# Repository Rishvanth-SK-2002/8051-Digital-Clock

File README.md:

# 8051 Digital Clock with Alarm

A bare-metal digital clock and alarm project built around the Nuvoton **W78E052DDG**, an 8051-compatible microcontroller. The project combines firmware, a custom two-layer through-hole PCB, display multiplexing, push-button UI, an audible alarm, and multiple PCB revisions.

## Project highlights

- Nuvoton W78E052DDG 8051-compatible MCU
- 11.0592 MHz clock source
- Six multiplexed 7-segment displays
- Six discrete BC547 digit drivers
- 6-position user interface: LEFT / RIGHT / UP / DOWN / MODE / TIMESET/ALARM selection
- Timer0-driven software time base
- External interrupt 0 used for entering configuration mode
- Alarm time comparison and buzzer output
- 2-layer through-hole PCB developed through multiple revisions
- Final PCB source, schematic, and manufacturing Gerbers included
- Firmware is written in 8051 assembly

## Repository structure

```text
.
├── firmware/
│   ├── digclock.asm
│   ├── MEMORY_MAP.md
│   ├── FIRMWARE_ARCHITECTURE.md
│   ├── README.md
├── hardware/
│   ├── schematic/
│   │   ├── digclock.kicad_sch
│   │   ├── digclock.kicad_pro
│   │   ├── digclock-eagle-import.kicad_sym
│   │   └── sym-lib-table
│   ├── pcb/
│   │   ├── final/
│   │   │   └── digclock.kicad_pcb
│   │   └── revisions/
│   │       ├── v1/digclockv1.kicad_pcb
│   │       ├── v2/digclockv2.kicad_pcb
│   │       ├── v3/digclockv3.kicad_pcb
│   │       └── v4/digclockv4.kicad_pcb
│   ├── fabrication/
│   │   ├── gerbers_final/
│   │   └── historical/
│   │       ├── v2/
│   │       └── v4/
│   ├── README.md
│   └── PCB_DESIGN_HISTORY.md
├── media/
│   └── Digclock_Enclosed.jpg
│   ├── Digclock_PCBA.jpg
│   ├── Digclock_PCB_Unassembled.jpg
│   └── Digclock_Breadboard.jpg
```

## Firmware architecture

The firmware uses two primary interrupts:

- **INT0 / P3.2**: enters the time/alarm setting interface and temporarily stops Timer0.
- **Timer0 overflow**: updates the software clock counters.

The main loop multiplexes the six displays and checks the alarm buffer against the current six-byte clock field.

The software time base uses Timer0 Mode 1 with a reload of **EFDBH**. That corresponds to 4133 timer counts. Assuming the project's 11.0592 MHz oscillator is operated in conventional 12T mode, one overflow is approximately 4.4846 ms and 223 overflows are nominally about 1.000064 s before accounting for exact interrupt/instruction overhead.

## Hardware architecture

The display uses a shared segment bus on **P0** and six digit-select controls on **P2.7 through P2.2**. The digit-select outputs drive six transistor stages so that only one display position is active at a time.

The user-interface and alarm connections are:

| MCU pin | Function |
|---|---|
| P1.0 | LEFT |
| P1.1 | RIGHT |
| P1.2 | UP |
| P1.3 | DOWN |
| P1.4 | BUZZER |
| P2.0 | ALARM mode select |
| P2.1 | TIMESET mode select |
| P3.2 / INT0 | MODE / configuration interrupt |
| P0 | 7-segment segment bus |
| P2.7..P2.2 | Digit select 1..6 |

## PCB development

The repository deliberately keeps the numbered PCB revisions because this was the first PCB project and the revisions document the design process. The revision history is described in `hardware/PCB_DESIGN_HISTORY.md`.

The current manufacturing output is in:

```text
hardware/fabrication/gerbers_final/
```

The final source PCB is:

```text
hardware/pcb/final/digclock.kicad_pcb
```

## Opening the KiCad project

Open `hardware/schematic/digclock.kicad_pro` in KiCad. The PCB can then be opened from the project or directly from `hardware/pcb/final/digclock.kicad_pcb`.

The revision `.kicad_pcb` files are retained as historical snapshots and do not need to be used for the final board.

## Important schematic note

For ease of schematic development and unavailability of the actual IC's symbol, an imported symbol of PIC MCU was used.

Before using the schematic as the starting point for a new design, verify the MCU pin mapping against the **W78E052DDG datasheet** and the final PCB routing.

## Photos / project presentation

Photos of the stage-by-stage progression of this project are uploaded for reference as mentioned below.

1. System wired using a breadboard.
2. PCB fabricated using the final version design but unassembled
3. Components Assembled PCB
4. Assembled PCB enclosed in a 3D-printed Enclosure.

The 3D-printed enclosure was designed by a collaborator.

## Engineering context

This project demonstrates a complete small embedded product workflow:

**requirements → schematic → PCB placement/routing → revision → firmware → bring-up/debug → assembled hardware → enclosure integration**

The firmware is intentionally retained at the assembly level so the implementation details of interrupts, timer configuration, register banks, indirect addressing, table lookup, multiplexing, and bare-metal UI logic remain visible.

## References

- Nuvoton W78E052D / W78E054D datasheet: https://www.nuvoton.com/resource-files/W78E054D_W78E052D_A13.pdf
- KiCad project files: see `hardware/`

## License

No license is asserted by this repository yet.

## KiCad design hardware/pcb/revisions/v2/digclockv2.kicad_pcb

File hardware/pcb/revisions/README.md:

# PCB Revisions

These files are historical KiCad PCB snapshots:

- `v1` — first large board implementation
- `v2` — major compact layout revision
- `v3` — intermediate placement/routing experiment
- `v4` — further physical/mechanical refinement

The current/final board is kept separately under `../final/`.

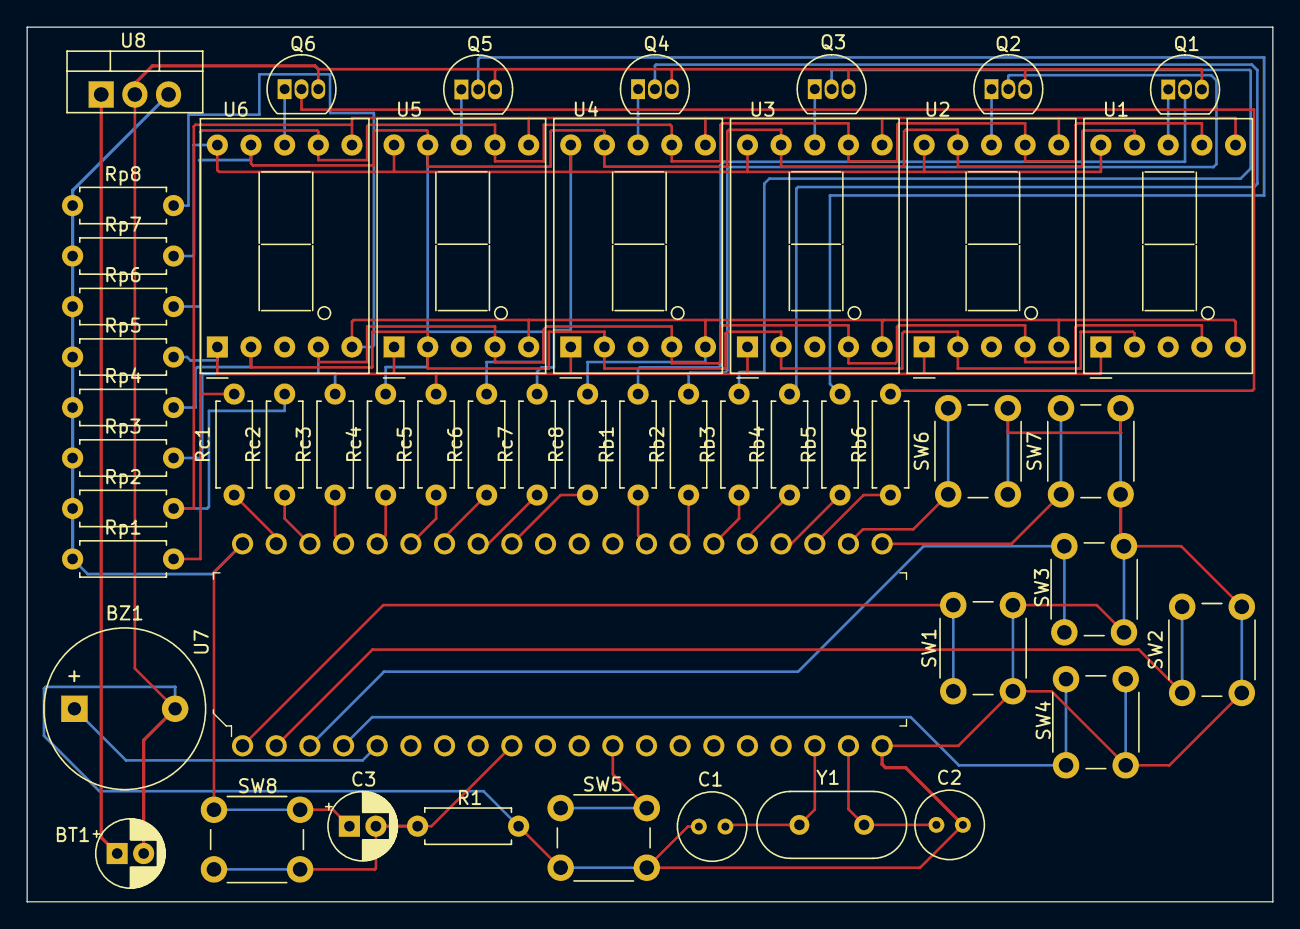
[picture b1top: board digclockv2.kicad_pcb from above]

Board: 2 copper layers, 94.0 x 66.0 mm, 51 parts (0 on the bottom side), 48 nets.

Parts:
BT1: 9V; CP_Radial_D5.0mm_P2.00mm
BZ1: Buzzer; Buzzer_12x9.5RM7.6
C1, C2: 33pF; C_Radial_D5.0mm_H5.0mm_P2.00mm
C3: 10uF; CP_Radial_D5.0mm_P2.00mm
Q1, Q2, Q3, Q4, Q5, Q6: BC547; TO-92_Inline
R1: 10k; R_Axial_DIN0207_L6.3mm_D2.5mm_P7.62mm_Horizontal
Rb1, Rb2, Rb3, Rb4, Rb5, Rb6: 1k; R_Axial_DIN0207_L6.3mm_D2.5mm_P7.62mm_Horizontal
Rc1, Rc2, Rc3, Rc4, Rc5, Rc6, Rc7, Rc8: 330; R_Axial_DIN0207_L6.3mm_D2.5mm_P7.62mm_Horizontal
Rp1, Rp2, Rp3, Rp4, Rp5, Rp6, Rp7, Rp8: 1k; R_Axial_DIN0207_L6.3mm_D2.5mm_P7.62mm_Horizontal
SW1: LEFT; SW_PUSH_6mm
SW2: RIGHT; SW_PUSH_6mm
SW3: UP; SW_PUSH_6mm
SW4: DOWN; SW_PUSH_6mm
SW5: MODE; SW_PUSH_6mm
SW6: TIMESET; SW_PUSH_6mm
SW7: ALARM; SW_PUSH_6mm
SW8: RESET; SW_PUSH_6mm
U1, U2, U3, U4, U5, U6: D168K; D1X8K
U7: W78E052DDG; DIP-40_W15.24mm
U8: LM7805; TO-220-3_Vertical
Y1: 11.0592Mhz; Crystal_HC49-U_Vertical

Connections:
unnamed: BT1.1 (+), U8.1 (VI)
unnamed: BT1.2 (-), BZ1.2 (+), C1.1, C2.1, Q1.3 (E), Q2.3 (E), Q3.3 (E), Q4.3 (E), Q5.3 (E), Q6.3 (E), R1.1, SW1.1, SW2.2, SW3.2, SW4.2, SW5.1, SW6.2, SW7.2, U7.20 (GND), U8.2 (GND)
unnamed: BZ1.1 (-), U7.5 (P1.4)
unnamed: C1.2, U7.18 (XTAL2), Y1.2
unnamed: C2.2, U7.19 (XTAL1), Y1.1
unnamed: C3.1, Rp1.1, Rp2.1, Rp3.1, Rp4.1, Rp5.1, Rp6.1, Rp7.1, Rp8.1, SW8.2, U7.40 (VCC), U8.3 (VO)
unnamed: C3.2, R1.2, SW8.1, U7.9 (RST)
unnamed: Q1.1 (C), U1.8 (CC)
unnamed: Q1.2 (B), Rb1.2
unnamed: Q2.1 (C), U2.8 (CC)
unnamed: Q2.2 (B), Rb2.2
unnamed: Q3.1 (C), U3.8 (CC)
unnamed: Q3.2 (B), Rb3.2
unnamed: Q4.1 (C), U4.8 (CC)
unnamed: Q4.2 (B), Rb4.2
unnamed: Q5.1 (C), U5.8 (CC)
unnamed: Q5.2 (B), Rb5.2
unnamed: Q6.1 (C), U6.8 (CC)
unnamed: Q6.2 (B), Rb6.2
unnamed: Rb1.1, U7.28 (P2.7(A15))
unnamed: Rb2.1, U7.27 (P2.6(A14))
unnamed: Rb3.1, U7.26 (P2.5(A13))
unnamed: Rb4.1, U7.25 (P2.4(A12))
unnamed: Rb5.1, U7.24 (P2.3(A11))
unnamed: Rb6.1, U7.23 (P2.2(A10))
unnamed: Rc1.1, U7.39 (P0.0(AD0))
unnamed: Rc1.2, Rp1.2, U1.7 (A), U2.7 (A), U3.7 (A), U4.7 (A), U5.7 (A), U6.7 (A)
unnamed: Rc2.1, U7.38 (P0.1(AD1))
unnamed: Rc2.2, Rp2.2, U1.6 (B), U2.6 (B), U3.6 (B), U4.6 (B), U5.6 (B), U6.6 (B)
unnamed: Rc3.1, U7.37 (P0.2(AD2))
unnamed: Rc3.2, Rp3.2, U1.4 (C), U2.4 (C), U3.4 (C), U4.4 (C), U5.4 (C), U6.4 (C)
unnamed: Rc4.1, U7.36 (P0.3(AD3))
unnamed: Rc4.2, Rp4.2, U1.2 (D), U2.2 (D), U3.2 (D), U4.2 (D), U5.2 (D), U6.2 (D)
unnamed: Rc5.1, U7.35 (P0.4(AD4))
unnamed: Rc5.2, Rp5.2, U1.1 (E), U2.1 (E), U3.1 (E), U4.1 (E), U5.1 (E), U6.1 (E)
unnamed: Rc6.1, U7.34 (P0.5(AD5))
unnamed: Rc6.2, Rp6.2, U1.9 (F), U2.9 (F), U3.9 (F), U4.9 (F), U5.9 (F), U6.9 (F)
unnamed: Rc7.1, U7.33 (P0.6(AD6))
unnamed: Rc7.2, Rp7.2, U1.10 (G), U2.10 (G), U3.10 (G), U4.10 (G), U5.10 (G), U6.10 (G)
unnamed: Rc8.1, U7.32 (P0.7(AD7))
unnamed: Rc8.2, Rp8.2, U1.5 (DP), U2.5 (DP), U3.5 (DP), U4.5 (DP), U5.5 (DP), U6.5 (DP)
unnamed: SW1.2, U7.1 (P1.0)
unnamed: SW2.1, U7.2 (P1.1)
unnamed: SW3.1, U7.3 (P1.2)
unnamed: SW4.1, U7.4 (P1.3)
unnamed: SW5.2, U7.12 (P3.2(~INT0))
unnamed: SW6.1, U7.22 (P2.1(A9))
unnamed: SW7.1, U7.21 (P2.0(A8))
